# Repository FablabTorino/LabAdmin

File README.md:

# LabAdmin

Manage user rights to access the lab and the machines

## Quickstart

Install the labAdmin:

```
python setup.py install
```

Add it to the installed apps:

```
INSTALLED_APPS = [
    # ...
    'rest_framework',
    'oauth2_provider',
    'labAdmin',
]
```

Add labAdmin urls to your project urls:

```
urlpatterns = [
    # ...
    include(r'^labAdmin/', include('labAdmin.urls')),
]
```

Profit!

### Settings

The optional MQTT integration has the following settings:

```
LABADMIN_MQTT_CONFIG = {
    'HOSTNAME': 'localhost',
    'PORT': 1883,
    'AUTH': None,
    'TLS': None,
    'PROTOCOL': MQTTv311,
    'TRANSPORT': 'tcp',
}

# Should we publish on MQTT each entrance
LABADMIN_NOTIFY_MQTT_ENTRANCE = False

# The MQTT topic where to publish
LABADMIN_MQTT_ENTRANCE_TOPIC = 'labadmin/entrance'
```

See [Paho MQTT documentation](https://github.com/eclipse/paho.mqtt.python#single) for `LABADMIN_MQTT_CONFIG` values.

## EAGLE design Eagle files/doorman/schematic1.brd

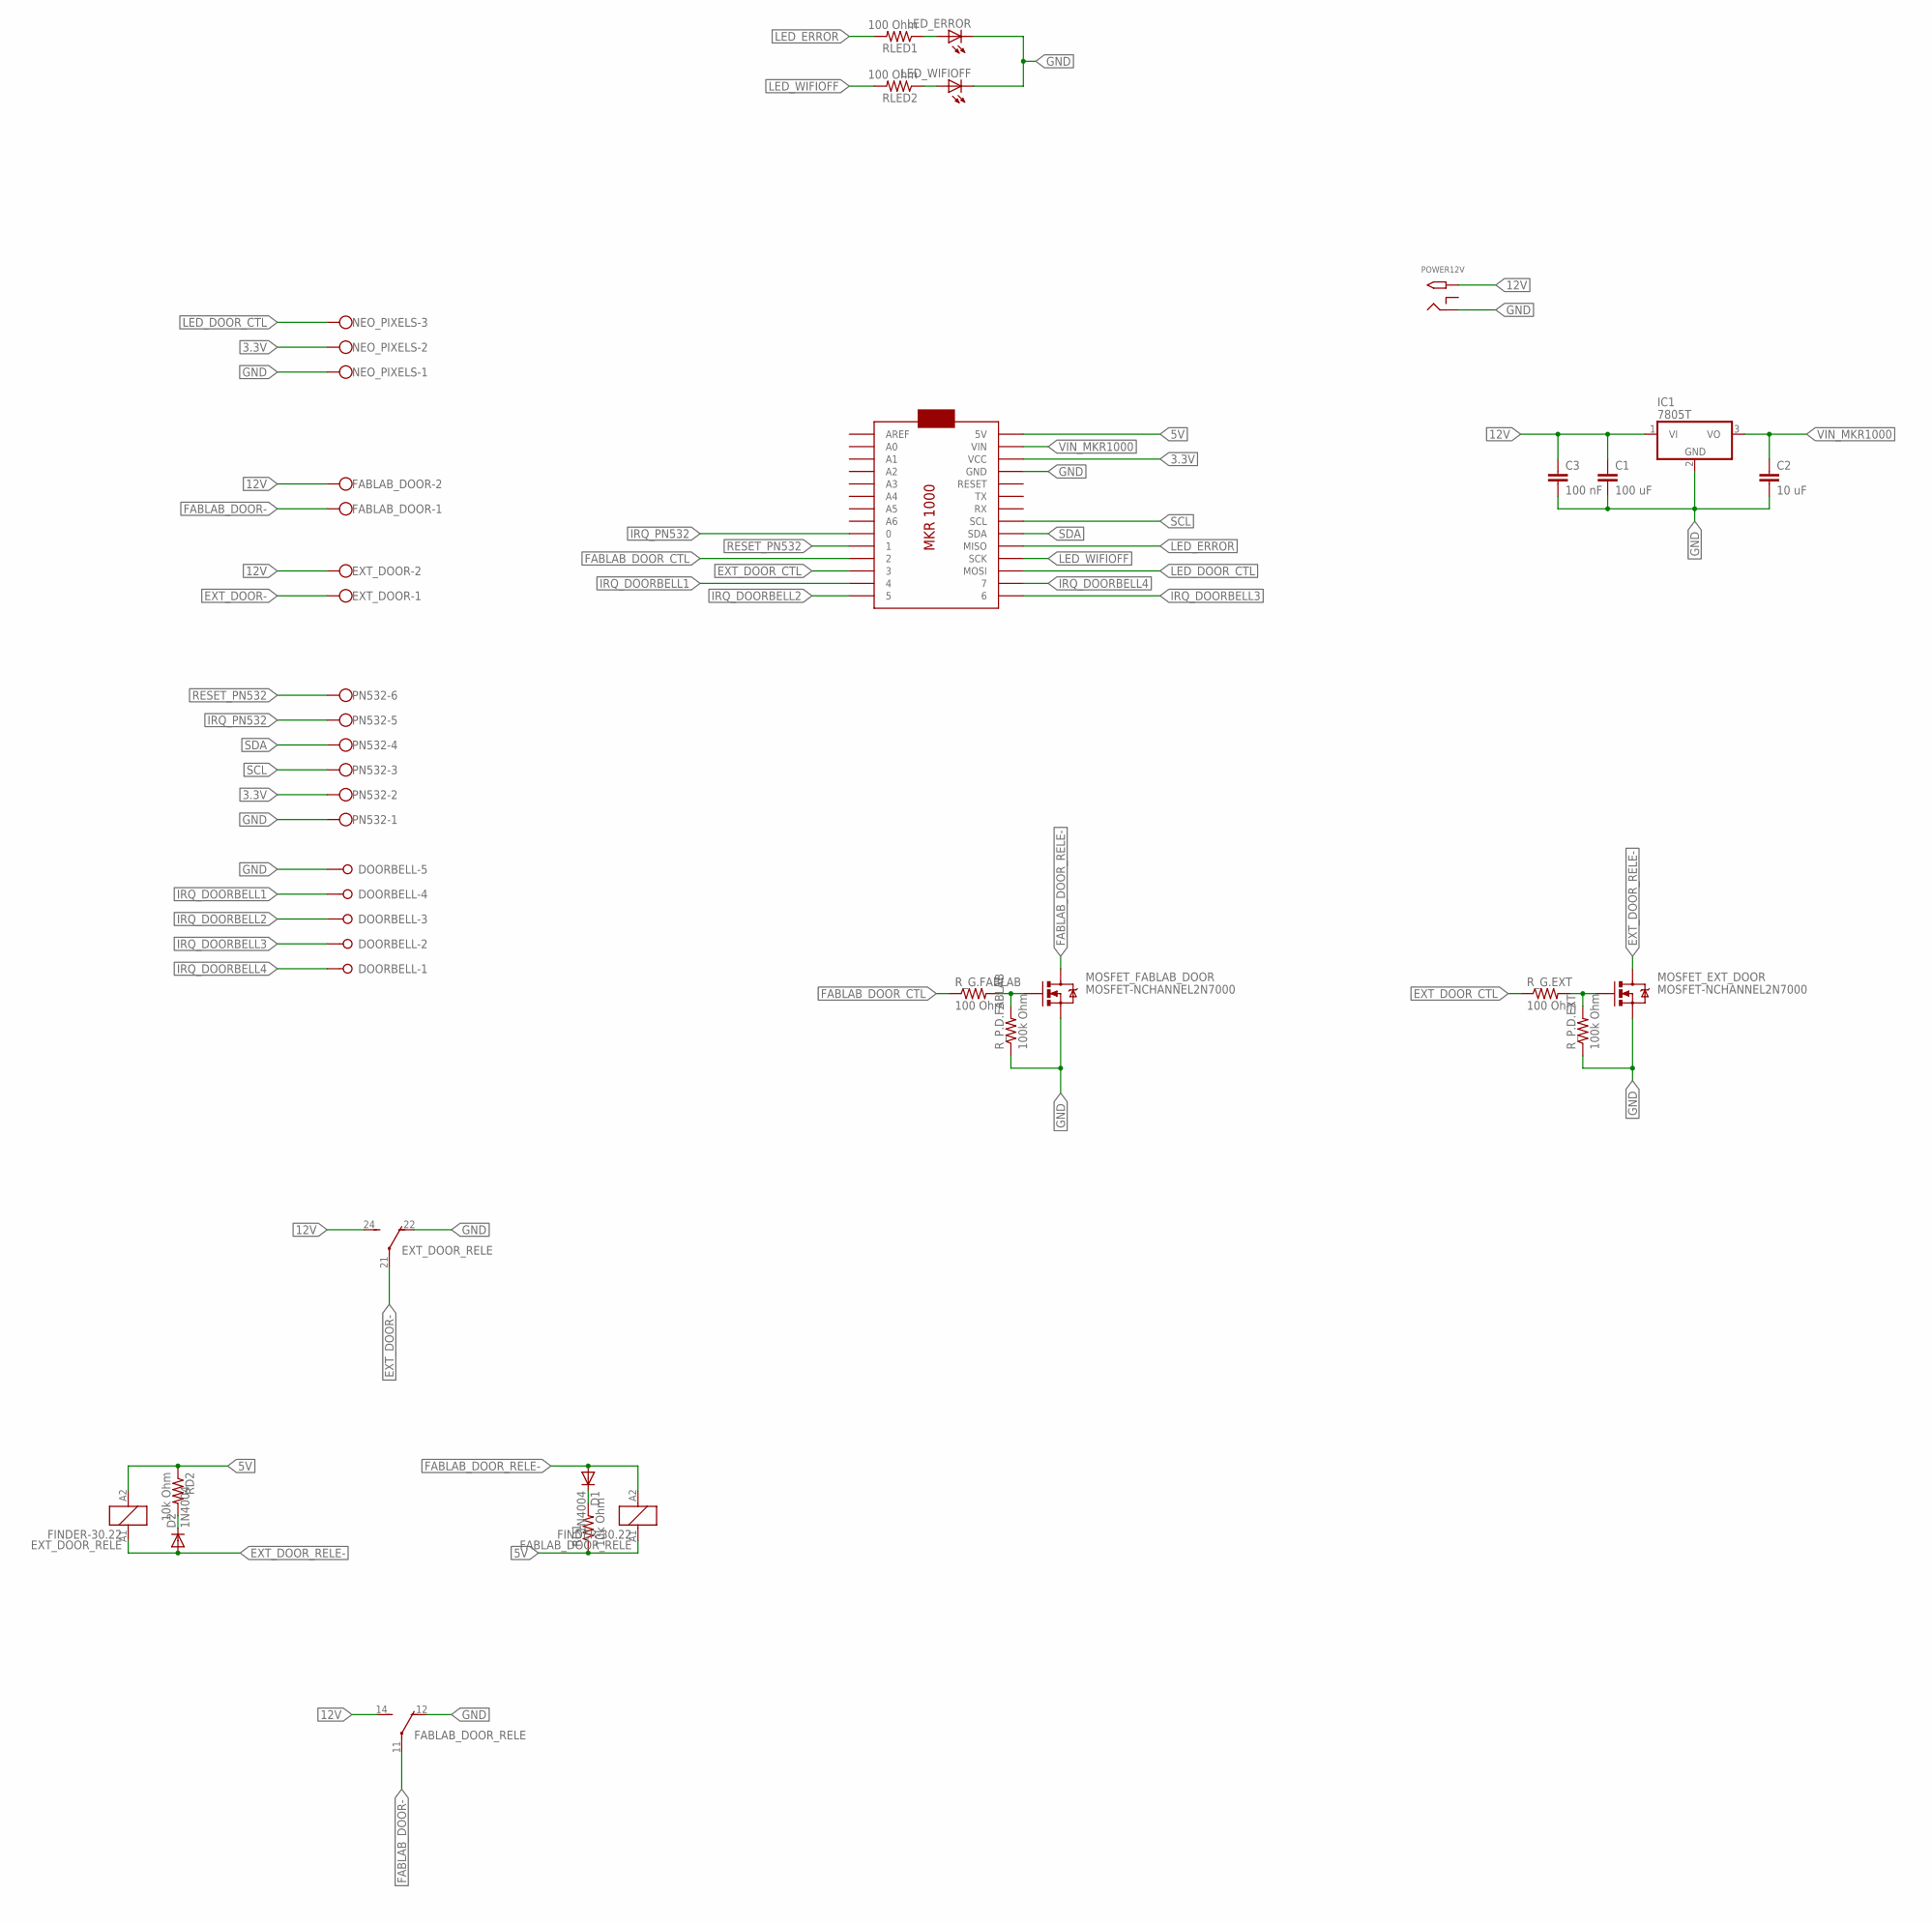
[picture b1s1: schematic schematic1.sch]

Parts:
C1: 100 uF; C2.5-2
C2: 10 uF; C2.5-2
C3: 100 nF; C2.5-2
D1, D2: 1N4004; DO41-10
DOORBELL: W237-05P; W237-5P
EXT_DOOR: W237-102
EXT_DOOR_RELE: FINDER-30.22
FABLAB_DOOR: W237-102
FABLAB_DOOR_RELE: FINDER-30.22
IC1: 7805T; TO220H
LED_ERROR: LED3MM
LED_WIFIOFF: LED3MM
MOSFET_EXT_DOOR: MOSFET-NCHANNEL2N7000; TO-92
MOSFET_FABLAB_DOOR: MOSFET-NCHANNEL2N7000; TO-92
NEO_PIXELS: W237-103
PN532: W237-136
POWER12V: 2.1MMJACKTHM; PJ-102A
RD1, RD2: 10k Ohm; 0207/10
RLED1, RLED2: 100 Ohm; 0207/10
R_G.EXT, R_G.FABLAB: 100 Ohm; 0207/10
R_P.D.EXT, R_P.D.FABLAB: 100k Ohm; 0207/10
U$1: ARDUINOMKR1000

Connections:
3.3V: NEO_PIXELS.2, PN532.2, U$1.VCC
5V: EXT_DOOR_RELE.A2 (2), FABLAB_DOOR_RELE.A1 (1), RD1.1, RD2.1, U$1.5V
12V: C1.1, C3.1, EXT_DOOR.2, EXT_DOOR_RELE.24 (S), FABLAB_DOOR.2, FABLAB_DOOR_RELE.14 (S), IC1.1 (VI), POWER12V.TIP
EXT_DOOR-: EXT_DOOR.1, EXT_DOOR_RELE.21
EXT_DOOR_CTL: R_G.EXT.1, U$1.3
EXT_DOOR_RELE-: D2.A, EXT_DOOR_RELE.A1 (1), MOSFET_EXT_DOOR.3 (D)
FABLAB_DOOR-: FABLAB_DOOR.1, FABLAB_DOOR_RELE.11
FABLAB_DOOR_CTL: R_G.FABLAB.1, U$1.2
FABLAB_DOOR_RELE-: D1.A, FABLAB_DOOR_RELE.A2 (2), MOSFET_FABLAB_DOOR.3 (D)
GND: C1.2, C2.2, C3.2, DOORBELL.5, EXT_DOOR_RELE.22 (O), FABLAB_DOOR_RELE.12 (O), IC1.2 (GND), LED_ERROR.K (C), LED_WIFIOFF.K (C), MOSFET_EXT_DOOR.1 (S), MOSFET_FABLAB_DOOR.1 (S), NEO_PIXELS.1, PN532.1, POWER12V.RING, R_P.D.EXT.1, R_P.D.FABLAB.1, U$1.GND
IRQ_DOORBELL1: DOORBELL.4, U$1.4
IRQ_DOORBELL2: DOORBELL.3, U$1.5
IRQ_DOORBELL3: DOORBELL.2, U$1.6
IRQ_DOORBELL4: DOORBELL.1, U$1.7
IRQ_PN532: PN532.5, U$1.0
LED_DOOR_CTL: NEO_PIXELS.3, U$1.MOSI
LED_ERROR: RLED1.2, U$1.MISO
LED_WIFIOFF: RLED2.2, U$1.SCK
unnamed: MOSFET_FABLAB_DOOR.2 (G), R_G.FABLAB.2, R_P.D.FABLAB.2
unnamed: MOSFET_EXT_DOOR.2 (G), R_G.EXT.2, R_P.D.EXT.2
unnamed: D2.C, RD2.2
unnamed: D1.C, RD1.2
unnamed: LED_ERROR.A, RLED1.1
unnamed: LED_WIFIOFF.A, RLED2.1
RESET_PN532: PN532.6, U$1.1
SCL: PN532.3, U$1.SCL
SDA: PN532.4, U$1.SDA
VIN_MKR1000: C2.1, IC1.3 (VO), U$1.VIN

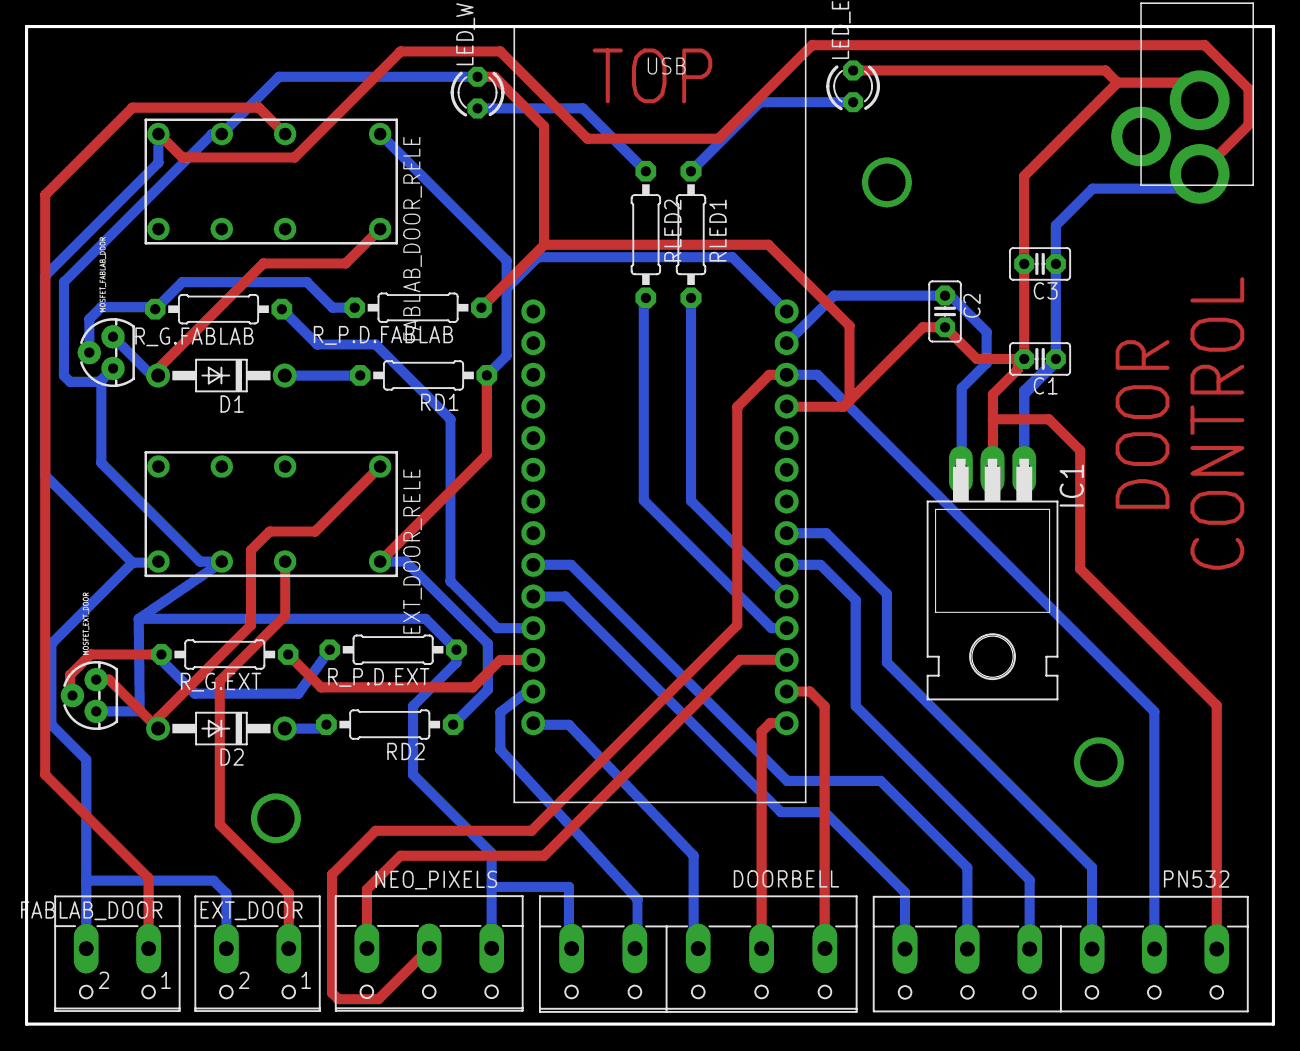
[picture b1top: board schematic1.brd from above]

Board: 2 copper layers, 100.0 x 80.0 mm, 27 parts (0 on the bottom side), 28 nets.

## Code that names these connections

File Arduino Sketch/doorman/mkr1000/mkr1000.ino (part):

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// Defining Pins
#define FABLAB_DOOR (2)
#define EXT_DOOR (3)
// #define IRQ_DOORBELL1 (4)
// #define IRQ_DOORBELL2 (5)
// #define IRQ_DOORBELL3 (6)
// #define IRQ_DOORBELL4 (7)
#define LED_DOOR (8)
#define LED_WIFIOFF (9)
#define LED_ERROR (10)

// Defining Constant

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
// Not Used
void setupIRQ() {
  pinMode(IRQ_DOORBELL1, INPUT_PULLUP);
  pinMode(IRQ_DOORBELL2, INPUT_PULLUP);
  // attachIRQ();
}

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  pinMode(FABLAB_DOOR, OUTPUT);
  pinMode(EXT_DOOR, OUTPUT);

  pinMode(LED_WIFIOFF, OUTPUT); digitalWrite(LED_WIFIOFF, LOW);
  pinMode(LED_ERROR, OUTPUT); digitalWrite(LED_ERROR, LOW);


  Serial.begin(115200);
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
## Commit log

2016-04-04 added user list to admin
2016-04-04 chancged app name
2016-04-04 aggiunto una linea
2016-04-04 Added new models
2016-04-05 Resolve import of poll labAdmin
2016-04-05 Add few labAdmin models methods
2016-04-05 Add method for opening the door and update db
2016-04-07 Aggiornato il database per prove in locale
2016-04-07 Add first REST API to open the door
2016-04-07 Remove Bug in views.py
2016-04-07 Resolve bugs
2016-04-11 Add new API
2016-04-12 Add Improvement
2016-04-12 added static files to be served by apache server on raspberry.
2016-04-14 nothing important
2016-04-22 Bug Nested Query Resolved
2016-05-16 last update
2016-05-30 Arduino Sketches
2016-06-11 Uploaded Eagle Files
2016-07-21 Revert "Merge pull request #5 from FablabTorino/alessandromnc"
2016-07-21 deleted Arduino and eagle files
2016-07-21 added more readme
2016-07-21 modified db credential
2016-07-24 finished guide to install django server locally
2016-09-21 models: rename User as UserProfile
    As the the users should be able to login we need a fk to django
    contrib.auth's User.
2016-09-21 models: add a few more field to the userprofile
    Add address, bio, picture, tax code and vat_id optional fields.
2016-09-21 README: update instructions
    To match the one relevant for an app and not for a whole django
    project.
2016-09-21 tests: rework tests to something that resembles a test
    Even if there's not tests actually :|
2016-09-21 models: signup dates should be nullable
    As we should not need them when we create users
2016-09-21 urls: don't leak views into the project urls
    Instead import the urls from labAdmin app
2016-09-21 models: fix typos
2016-09-21 Use proper django app layout
    So that it is installable and the test project can run tests
2016-09-21 labAdmin: add missing migrations
2016-09-22 utils: add fablabto specific utils
    One script to scrape the current plone server and another
    one to import dumped data here.
2016-09-27 setup: fix project url
2016-09-27 Hook oauth2 server machinery in the test project
2016-10-05 labAdmin: Add crude login template
    We need to hook login url that does not ship with a template so if
    the project where we are installed does not have one provide
    ourselves.
    Hook django login and logout views to our testSite so we can
    test the oauth2 integration.
2016-10-05 labAdmin: add view to serve user data from an oauth token
    This is neede for rocket.chat integration.
    While at it update README and setup with the django-oauth-toolkit
    dependency.
2016-10-05 labAdmin: add link to reset password to login template
    And hook reset views on the test project
2016-10-11 utils/fablabto: rework import script for Card rework
2016-10-11 labAdmin: rework user and card associations
    The same card could be used by more than one user so move the
    card to its own model and add foreign key to it from the
    user profile.
    While at it add tests for the views.
2016-10-11 labAdmin: refactor timeslot permission checking
    Let the db do the hard work when checking permissions using exists()
    and move the date handling to a custom manager in the TimeSlot
    class.
2016-10-11 labAdmin: add credits to Card model
2016-10-11 labAdmin: add api to read and update credits
    Add an endpoint to read via GET and update via POST the credits
    for a card given its nfc_id.
    Also log each update of credits, both from the api and the admin.
2016-10-12 labAdmin: fix Subscription typos
2016-10-12 labAdmin: make card a OneToOne for UserProfile
    We want to really enforce each user to have one card each
2016-10-12 labAdmin: allow only negative amount for credit update api
2016-10-18 setup: fix typo in install requires
2016-10-18 Add MANIFEST.in
    So that we correctly package everything we need.
2016-10-20 labAdmin: introduce permissions for device based on token
    Devices must add an HTTP Authorization header with a specific
    token:
    Authorization: Token <token>
2016-10-20 utils: add instructions for scraping the fablabto plone app
2016-12-20 labAdmin: fix UserProfile's can_open_door_now
    So it does what is supposed to do instead of hiding exceptions.
2016-12-21 Arduino Yun client for open door with nfc card
    Arduino yun sketch and python script for forwarding POST request to labadmin server in order to open the door by means of nfc card
2017-01-07 Rename Side Devices/yunDoorOpener/labAdminYunSketch.ino to yunDoorSystem/labAdminYunSketch.ino
2017-01-07 Rename Side Devices/yunDoorOpen/labAdminYunPythonScript.py to yunDoorSystem/labAdminYunPythonScript.py
2017-01-12 labAdmin: order card by nfc_id in admin
    In reverse order, so newer are on top.
    Fix #19
2017-01-12 labadmin: show username of card owner in admin
    And add it to searchable fields.
    Fix #24
2017-01-12 labAdmin: fix tests on thursday
    Move the timeslot manager tests on their own test case so that
    fixtures don't interfere. Fix running tests on thursday :)
2017-01-12 labAdmin: show devices available on the network
    When creating a new device in the admin show the list of devices
    we have on our arp cache.
    Visualization is a bit rough but works fine.
    Fix #27
2017-01-12 labAdmin: cleanup LogDevice stop
    While at it add a test
2017-01-12 labAdmin: show device last activity in admin
    Fix #26
2017-01-12 labadmin: make some sense of LogDevice.priceWork
    And add a test
2017-01-17 labAdmin: move token extraction from request into an helper
    As it will be handy for views needing a device.
2017-01-17 labadmin: add view to start logging the use of a device
    It takes the user card nfc id as nfc_id through a POST request.
    Ref #26
2017-01-17 labAdmin: fix UserProfile.can_use_device_now
    Like it actually works and doesn't silently fail under a catch all
    try block.
2017-01-17 labAdmin: add view to stop logging the use of a device
    It takes the user card nfc id as nfc_id through a POST request.
    Ref #26
2017-01-17 labAdmin: remove unused functions
    And remove duplicated import while at it.
2017-01-18 labAdmin: kill role kind
    We now treats doors as devices which means that we can kill the
    role_kind and the various can_use_door_now methods.
    So now OpenDoorByNFC requires the the token authentication as
    the credits API.
2017-01-18 labAdmin: kill unused can_use_device_now
    We don't need them and probably they aren't working either.
2017-01-24 labAdmin: remove unused data from tests fixture
2017-01-24 labAdmin: add tests for UserProfile.can_use_device_now()
2017-01-24 labAdmin: remove commented routes in urls
2017-01-24 labAdmin: check categories in can_use_device_now
    So that we can implement per category of device permission and
    not just for roles.
2017-01-31 labAdmin: fix tests on thursday (#4)
    Move the timeslot manager tests on their own test case so that
    fixtures don't interfere. Fix running tests on thursday :)
2017-01-31 labAdmin: remove star imports
2017-01-31 labAdmin: remove tempUpdateUser
    Looks like it solved a temporary need with a lot of assumptions
    on the local installation.
    If there's still need for something like that better use a
    management command.
2017-01-31 Don't ignore compiled translations
    As it's not trivial to build them at install time
2017-01-31 labAdmin: add mqtt notifications for entrance
    Add a way to notify positive entrances via MQTT. The notified
    payload is a json object with the following attributes:
    - user: string
    - event: string
    This integration is off by default.
2017-02-01 labAdmin: fix test_open_door_by_nfc_mqtt_error_log
    We have to reread the settings in the actual view so the
    override_settings works.
2017-02-01 labAdmin: add missing comma in setup.py
    Brown paper bug for me
2017-02-01 Hook machinery to run tests on travis-ci.org
2017-02-01 labAdmin: add django-cors-middleware dependency
    As it's used in the testSite settings better have it there
2017-02-01 labAdmin: fix import for older django

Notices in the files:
parts and their libraries:
SparkFun-DiscreteSemi: Licensing: Creative Commons ShareAlike 4.0 International - https://creativecommons.org/licenses/by-sa/4.0
